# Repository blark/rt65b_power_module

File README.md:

# rt65b_power_module

This is a power input/output board for the Mean Well RT65-B power supply.

This supply is commonly used as a replacement for the Amiga 500 power supply.

## Ordering

If you'd like to quickly order some boards I [published the project at Oshpark](https://oshpark.com/shared_projects/TvA0zYfn)

## BOM

The AC power entry module footprint is a Schurter KP01.1112.11 and the DC output is a circular DIN-7.

## Warning

USE EXTREME CAUTION WITH AC POWER! YOU COULD EASILY KILL YOURSELF IF YOU DON'T KNOW WHAT YOU'RE DOING.

Don't use this without an appropriate case/shielding to prevent possible injury and shock. In fact don't use it if you don't know exactly what you're doing.

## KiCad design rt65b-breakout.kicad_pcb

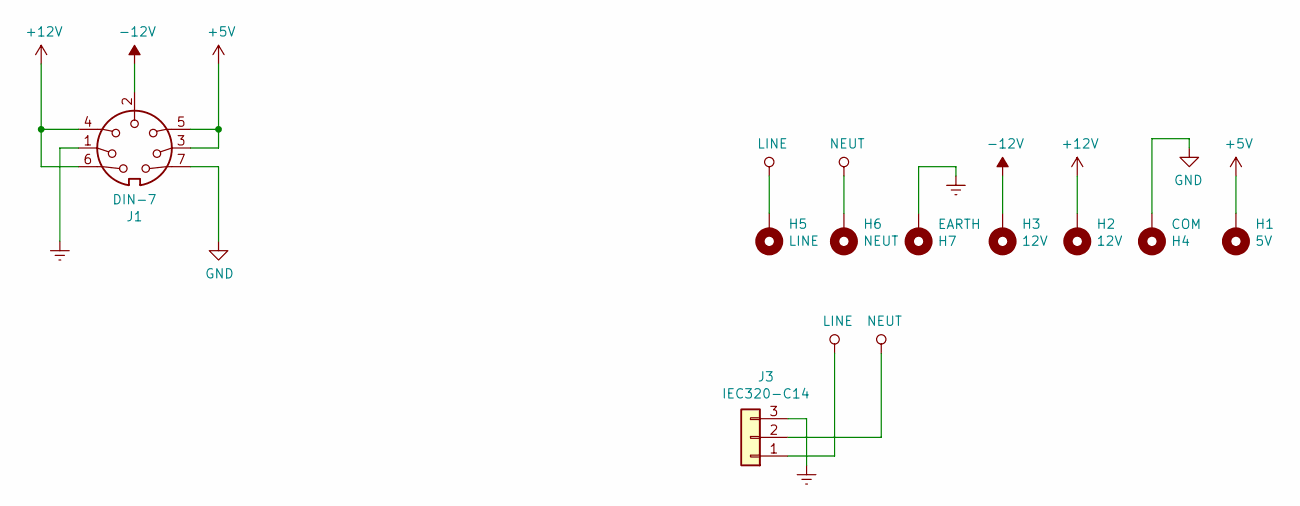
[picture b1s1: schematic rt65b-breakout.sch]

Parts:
H1: 5V; MountingHole_3mm_Pad_Via
H2, H3: 12V; MountingHole_3mm_Pad_Via
H4: COM; MountingHole_3mm_Pad_Via
H5: LINE; MountingHole_3mm_Pad_Via
H6: NEUT; MountingHole_3mm_Pad_Via
H7: EARTH; MountingHole_3mm_Pad_Via
J1: DIN-7
J3: IEC320-C14; KP01.1112.11

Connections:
+5V: H1.1, J1.3, J1.5
+12V: H2.1, J1.4, J1.6
-12V: H3.1, J1.2
Earth: H7.1, J1.1, J1.8, J1.9, J1.10, J3.3
GND: H4.1, J1.7
LINE: H5.1, J3.1
NEUT: H6.1, J3.2

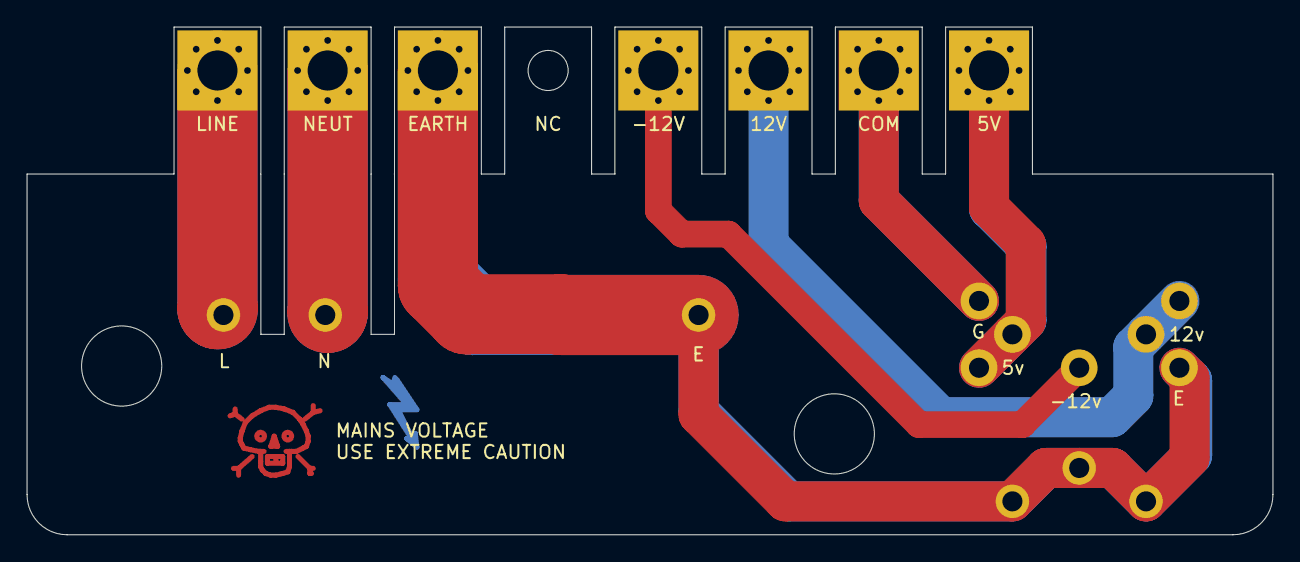
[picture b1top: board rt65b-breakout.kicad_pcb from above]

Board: 2 copper layers, 93.2 x 38.0 mm, 9 parts (0 on the bottom side), 7 nets.

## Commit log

2020-01-17 added pics
2020-01-17 added ordering info
2020-01-17 derp
2020-01-18 added back layer gnd trace
2020-01-18 update oshpark link
2020-01-18 updated gerbers
